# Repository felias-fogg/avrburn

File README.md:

# avrburn

This sketch turns your Gambuino META into a mobile AVR programmer.

## Features

This programmer lets you program most of the AVR ATmega and ATtiny MCUs, at least all of those
that support ISP programming and are listed in Atmel Studio 7.0. Just put the HEX files in the
folder BURN on your SD card and off you go.

## Usage

Any file with a **HEX** extension will be recognized as an a file to be programmed to flash memory, any file with an **EEP** extension as a file to be programmed into EEPROM, any file with a **FUS** extension will be used as a fuse file, and any file with a **LCK** extension as a lockbits file. The former two file types use the familiar ihex format, which you get, for instance, when you request to **Export Compiled Binary** in Arduino's **Sketch** menu. Fuse and lockbit files simply list the fuses or lockbits in hexadecimal, one per line, starting with the low fuse. There are some examples in the BURN folder.

The menus should be pretty much self-explanatory. In the **Settings** menu, you can set whether you want to have automatic verification and automatic erasure before programming, both of which is enabled by default. The **Safe Fuse Editting** option makes sure that you cannot edit fuses that make the MCU unresponsive. Finally, you can choose the SPI clock frequency. 100 kHz is a good compromise between speed and robustness. However, in general, you can chose any clock that is not higher than a quarter of the MCU clock frequency. 

Navigating through the menus is done with the **up** and **down** buttons as well as the **A** button to select an entry. Pressing the **B** button exits the current menu. Pressing the **Menu** button restarts the sketch.

## Electrical connection

Currently, the following Gamebuino-Meta pins are used:
* Port D2 (PA14): Reset
* Port D3 (PA09): MOSI
* Port D4 (PA08): SCK
* Port D5 (PA15): MISO

In addition, Vcc and GND are connected. You have to connect
these pins with the corresponding pins on the target system. It is, of course, possible to use other pins. But then you have to change the corresponding definitions in avrburn.ino. 

**BEWARE**: If you connect the pins directly to the target system, make sure that you connect only to
3.3 Volt systems. Because the Gamebuino Meta is not 5 Volt tolerant, it will get damaged if
connected to a 5 Volt system. If you have a chip in a programming socket and the Gambuino supplies the current, then there won't be any problem (not possible anymore!). 

There exists now a PCB that can be plugged into the Meta, which does the level shifting if necessary. In other words, you can now also program 5 volt systems!

## Planned additions

The following things are planned for the future:
* Porting the program to ODROID GO (not so sure anymore)

The software is published under the [LGPL](http://www.gnu.org/licenses/lgpl-3.0.html).

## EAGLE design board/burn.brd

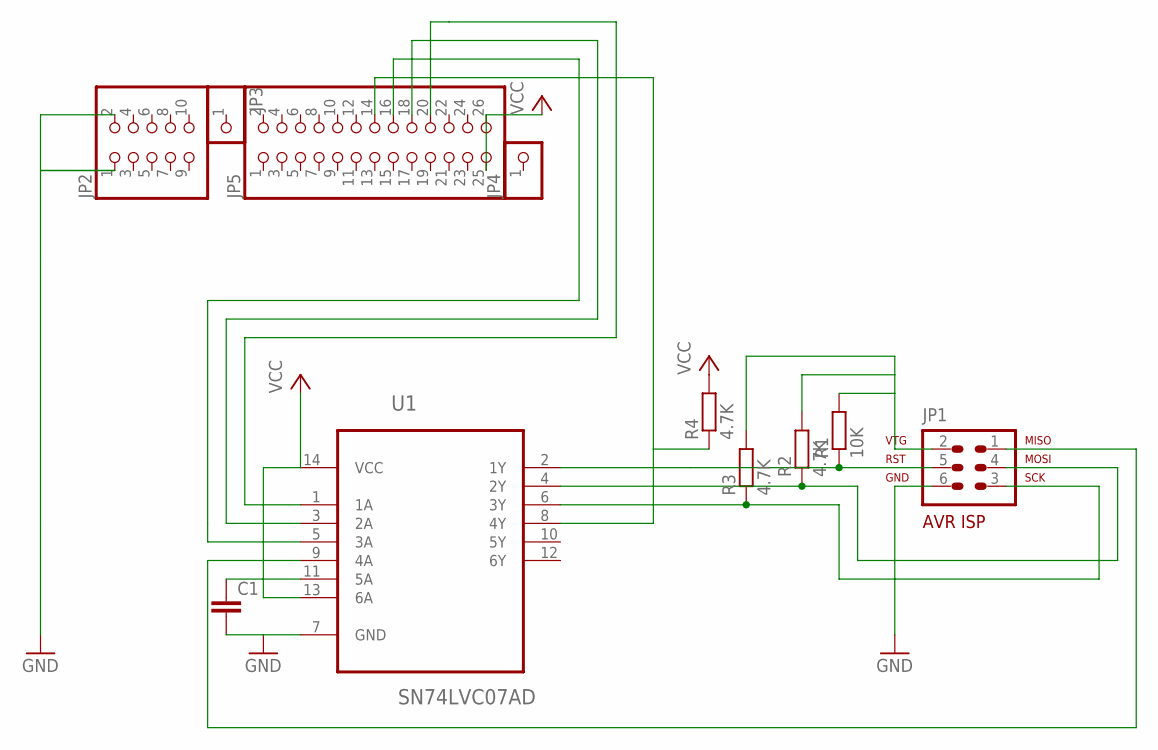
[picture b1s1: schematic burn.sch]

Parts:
C1: C-EUC1206K; C1206K
JP1: AVR-ISP; AVR-ISP-6
JP2: PINHD-2X5; 2X05
JP3, JP4: PINHD-1X1; 1X01
JP5: PINHD-2X13; 2X13
R1: 10K; R1206W
R2, R3, R4: 4.7K; R1206W
U1: SN74LVC07AD; SOIC127P600X175-14N

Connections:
GND: C1.2, JP1.6, JP2.1, JP2.2, U1.7 (GND)
unnamed: JP5.16, U1.5 (3A)
unnamed: JP1.5, R1.1, U1.2 (1Y)
unnamed: JP5.20, U1.1 (1A)
unnamed: JP5.18, U1.3 (2A)
unnamed: JP1.4, R2.1, U1.4 (2Y)
unnamed: JP1.3, R3.1, U1.6 (3Y)
unnamed: JP5.14, R4.1, U1.8 (4Y)
unnamed: JP1.1, U1.9 (4A)
unnamed: JP1.2, R1.2, R2.2, R3.2
VCC: C1.1, JP5.25, JP5.26, R4.2, U1.11 (5A), U1.13 (6A), U1.14 (VCC)

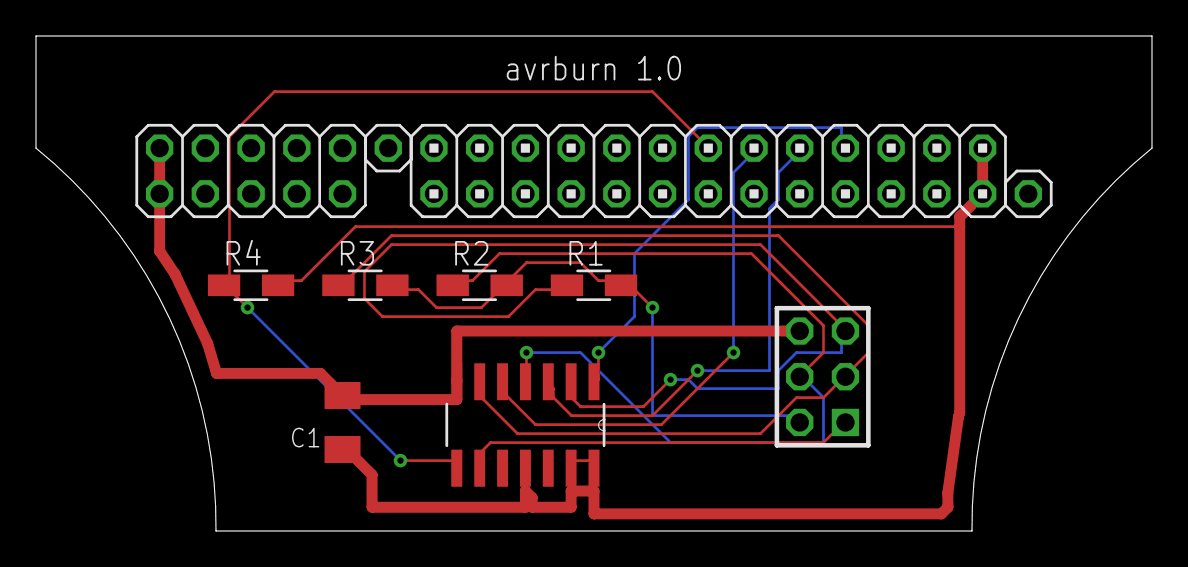
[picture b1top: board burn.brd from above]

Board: 2 copper layers, 62.0 x 27.5 mm, 11 parts (0 on the bottom side), 11 nets.

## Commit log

2019-02-10 V0.1
2019-02-11 V0.2
2019-02-13 V0.3
2019-02-17 V0.4 - fuses and lock bits can be set
2019-02-25 V0.5 - save works for all cats
2019-02-28 V0.6a - prepared for flash/eeprom programming
2019-02-28 V0.6 - programming works
2019-03-01 V0.7c - flash + eeprom progrramming works / problem with non-paged MCUs
2019-03-02 V0.7 - everything works / no fuse editing yet
2019-03-02 V0.8 - new SPI speeds
2019-03-03 changes before going public
2019-03-03 V0.9d (Debug disabled)
2019-03-04 V0.9.1 - fuse editing works / some fuses are not yet defed
2019-03-04 correction
2019-03-05 V0.9.3
2019-03-06 V0.9.4
    Everyting works - there are probably still bugs, though
2019-03-21 V0.9.5 - level-shifter designed and integrated
2019-04-20 Hardware ready!
